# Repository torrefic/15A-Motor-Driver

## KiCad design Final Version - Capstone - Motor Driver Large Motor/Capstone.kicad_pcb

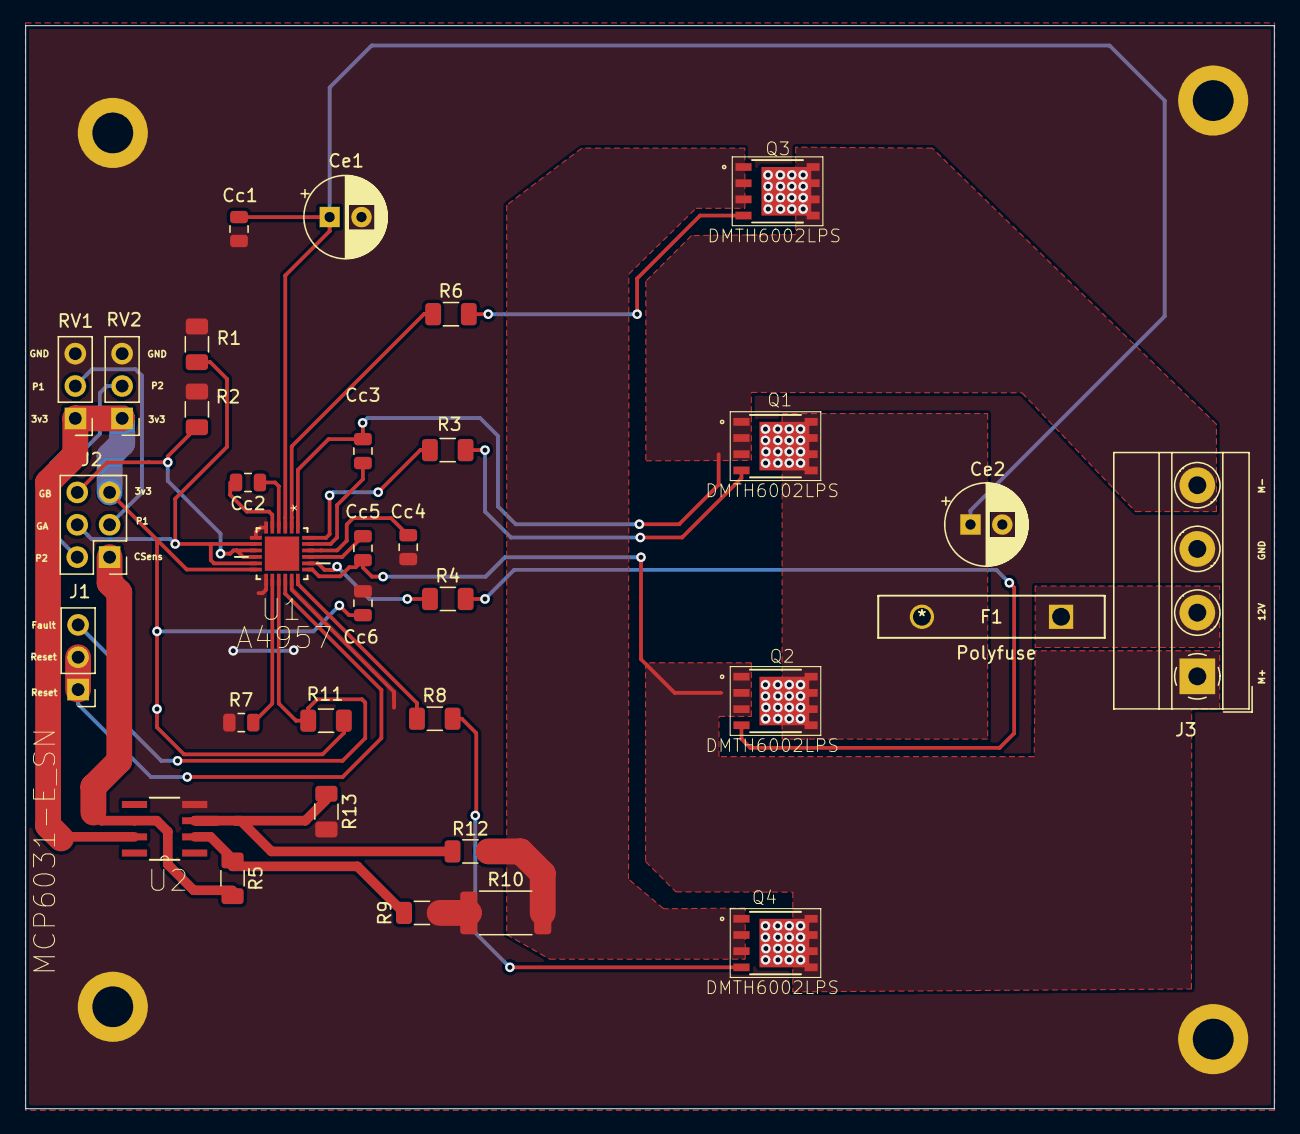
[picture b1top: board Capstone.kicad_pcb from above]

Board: 2 copper layers, 98.0 x 85.0 mm, 33 parts (0 on the bottom side), 30 nets.

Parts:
Cc1, Cc6: 100nF; C_0805_2012Metric
Cc2: 470nF; C_0805_2012Metric
Cc3, Cc5: 120nF; C_0805_2012Metric
Cc4: 1uF; C_0805_2012Metric
Ce1, Ce2: 50uF; CP_Radial_D6.3mm_P2.50mm
F1: Polyfuse; RGEF1200
J1: Conn_01x03_Male; PinHeader_1x03_P2.54mm_Vertical
J2: Conn_02x03_Odd_Even; PinHeader_2x03_P2.54mm_Vertical
J3: Screw_Terminal_01x04; TerminalBlock_MetzConnect_Type011_RT05504HBWC_1x04_P5.00mm_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
Q1, Q2, Q3, Q4: DMTH6002LPS; LargeMotorMosfets
R1, R2, R3, R4, R6, R8, R9, R12: 2.49k; R_1206_3216Metric
R5, R13: 698k; R_1206_3216Metric
R7: 3k; R_0805_2012Metric
R10: 0.4; R_2512_6332Metric
R11: 33k; R_1206_3216Metric
RV1, RV2: Motor Joint Potentiometer; PinHeader_1x03_P2.54mm_Vertical
U1: A4957; QFN50P400X400X80-25N
U2: MCP6031-E_SN; SOIC127P600X175-8N

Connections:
Earth: Cc1.2, Cc4.1, Cc6.2, Ce1.2, Ce2.2, J3.3, R1.2, R2.2, R7.2, R9.1, R10.1, R13.2, RV1.3, RV2.3, U1.6, U1.7, U1.13, U1.17, U2.4
unnamed: Cc1.1, Ce1.1, Ce2.1, F1.2, Q1.5, Q1.6, Q1.7, Q1.8, Q1.9, Q2.5, Q2.6, Q2.7, Q2.8, Q2.9, U1.3
unnamed: Cc2.1, U1.4
unnamed: Cc2.2, U1.5
unnamed: Cc3.1, J3.4, Q1.1, Q1.2, Q1.3, Q3.5, Q3.6, Q3.7, Q3.8, Q3.9, U1.1
unnamed: Cc3.2, U1.23
unnamed: Cc4.2, U1.22
unnamed: Cc5.1, J3.1, Q2.1, Q2.2, Q2.3, Q4.5, Q4.6, Q4.7, Q4.8, Q4.9, U1.19
unnamed: Cc5.2, U1.21
unnamed: Cc6.1, J2.5, R11.2, RV1.1, RV2.1, U1.12, U2.7
unnamed: F1.1, J3.2
unnamed: J1.1, J1.2, U1.16
unnamed: J1.3, R11.1, U1.15
unnamed: J2.1, R5.2, U2.6
unnamed: J2.2, RV2.2
unnamed: J2.3, RV1.2
unnamed: J2.4, R1.1, U1.8, U1.11
unnamed: J2.6, R2.1, U1.9, U1.10
unnamed: Q1.4, R3.2
unnamed: Q2.4, R4.2
unnamed: Q3.1, Q3.2, Q3.3, Q4.1, Q4.2, Q4.3, R10.2, R12.1
unnamed: Q3.4, R6.2
unnamed: Q4.4, R8.2
unnamed: R3.1, U1.24
unnamed: R4.1, U1.20
unnamed: R5.1, R9.2, U2.2
unnamed: R6.1, U1.2
unnamed: R7.1, U1.14
unnamed: R8.1, U1.18
unnamed: R12.2, R13.1, U2.3

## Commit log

2019-04-02 Add files via upload
    This H-Bridge PCB uses the Allegro "A4957: Full Bridge MOSFET Driver" as a gate driver for 4 N-MOSFETs. The board is rated for 15A without heatsinks on the MOSFETs, but can sink larger currents depen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
    This board was developped using KiCad software and was ordered on https://jlcpcb.com/m with the following settings:
    Lead Free Surface Finish
    With Laser Stencil

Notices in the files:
Final Version - Capstone - Motor Driver Large Motor/Capstone.kicad_pcb:
License: CC BY 4.0
parts and their libraries:
Copyright 2016 Accelerated Designs. All rights reserved.
